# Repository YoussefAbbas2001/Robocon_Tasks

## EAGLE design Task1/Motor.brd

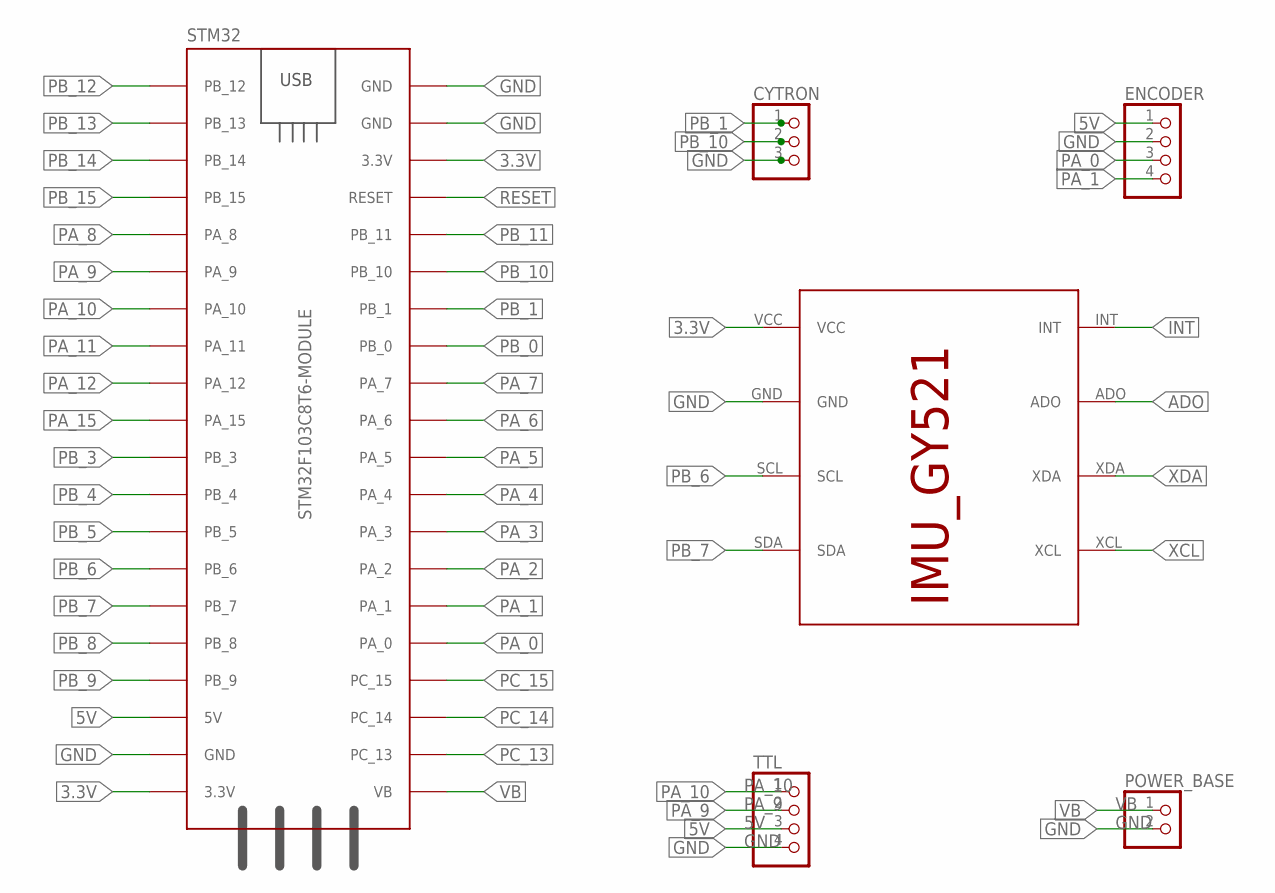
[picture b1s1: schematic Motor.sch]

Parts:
CYTRON: PINHD-3_DATA; 1X03_DATA
ENCODER: PINHD-4_DATA; 1X04_DATA
IMU: IMU_ROBOCON_GY521; IMU_GY521
POWER_BASE: PINHD-2_DATA; 1X02_DATA
STM32: STM32F103C8T6-MODULE
TTL: PINHD-4_DATA; 1X04_DATA

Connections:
3.3V: IMU.VCC, STM32.3.3V_1 (3.3V), STM32.3.3V_2 (3.3V)
5V: ENCODER.1, STM32.5V, TTL.3
ADO: IMU.ADO
GND: CYTRON.3, ENCODER.2, IMU.GND, POWER_BASE.2, STM32.GND_1 (GND), STM32.GND_2 (GND), STM32.GND_3 (GND), TTL.4
INT: IMU.INT
PA_0: ENCODER.3, STM32.PA_0
PA_1: ENCODER.4, STM32.PA_1
PA_2: STM32.PA_2
PA_3: STM32.PA_3
PA_4: STM32.PA_4
PA_5: STM32.PA_5
PA_6: STM32.PA_6
PA_7: STM32.PA_7
PA_8: STM32.PA_8
PA_9: STM32.PA_9, TTL.2
PA_10: STM32.PA_10, TTL.1
PA_11: STM32.PA_11
PA_12: STM32.PA_12
PA_15: STM32.PA_15
PB_0: STM32.PB_0
PB_1: CYTRON.1, STM32.PB_1
PB_3: STM32.PB_3
PB_4: STM32.PB_4
PB_5: STM32.PB_5
PB_6: IMU.SCL, STM32.PB_6
PB_7: IMU.SDA, STM32.PB_7
PB_8: STM32.PB_8
PB_9: STM32.PB_9
PB_10: CYTRON.2, STM32.PB_10
PB_11: STM32.PB_11
PB_12: STM32.PB_12
PB_13: STM32.PB_13
PB_14: STM32.PB_14
PB_15: STM32.PB_15
PC_13: STM32.PC_13
PC_14: STM32.PC_14
PC_15: STM32.PC_15
RESET: STM32.RESET
VB: POWER_BASE.1, STM32.VB
XCL: IMU.XCL
XDA: IMU.XDA

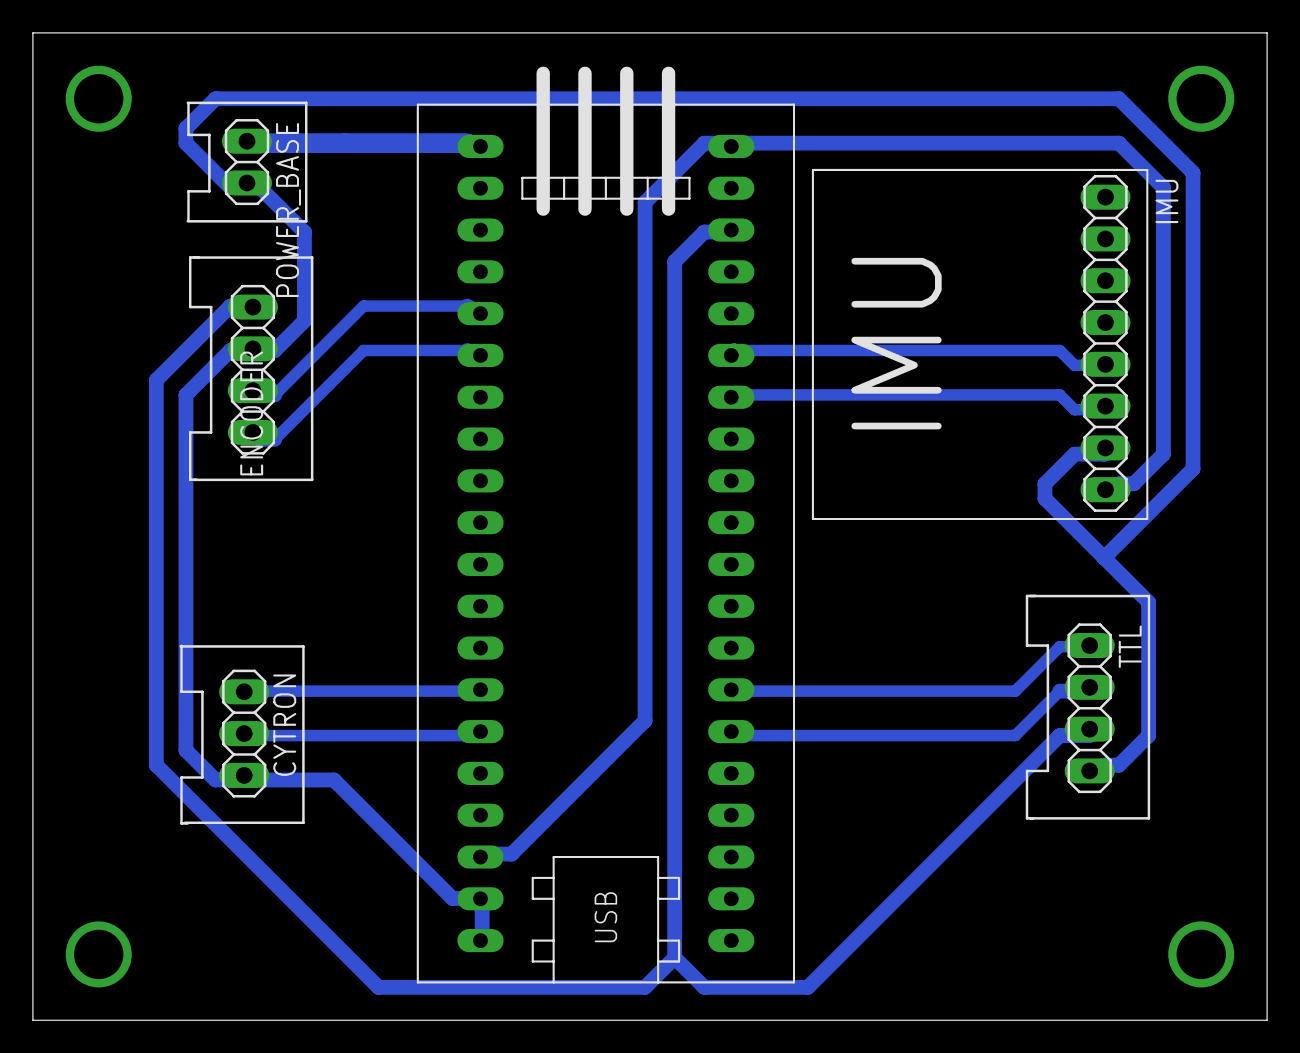
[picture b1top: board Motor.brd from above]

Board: 2 copper layers, 75.0 x 60.0 mm, 6 parts (0 on the bottom side), 12 nets.

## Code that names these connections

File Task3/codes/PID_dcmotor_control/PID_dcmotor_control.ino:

/*
Author : Youssef Abbas 
Date   : 6/11/2021
About  : PID control DC Motor
TO     : ROBOCON Traning Task3
*/
//#include <ros.h>
//#include <std_msgs/Float64.h>

#define SIGNAL_A PA_0  //PA_0
#define SIGNAL_B PA_1  //PA_1
#define PWM      PB_10 //PB_10
#define DIR      PB_1  //PB_1
#define PWM_LIM  65536 //Limit of PWM signal
#define PPRC     512   //Pulse Per Revolution Cycle
#define MIN      60    //minute

//ros::NodeHandle nh;
//float target;
//void callback( const std_msgs::Float64& msg){ target = msg.data;}
//ros::Subscriber<std_msgs::Float64> sub("drive_motor", &callback );

double  pwm      ;         //PWM signal  of MOTOR
double  control  ;         //Control Signal Out of PID control 
double  set_point= 0    ;  //target speed
double  integral = 0    ;  //Summation of error Added to control signal to overcome Steady-State Error
double  diff     = 0    ;  //Derivative term
double  kp =  2  ;         //Proportional Constant
double  ki =  1  ;         //Intergral Constant
double  kd =  1  ;         //Derivative Constant
double  error=0  ;         //Error Signal (E = T - P)
double  prev_e=0 ;         //previous error (to compute Derivaitve term)
double  velocity ;         //Current Velocity of Motor
double  distance ;         //Distance cutted by Motor in Meter
double  delta_t  ;         //Change time = (current time) - (previous time)
double  delta_e  ;         //Change Error= (Current error)- (previous error)
double  prev_t=0 ;         //Previous time used to computer delta of time 
double  curr_t=0 ;         //Current time usef to compute  delta of time
double  counter=0;         //Counter of Encoder
double  prev_c=0 ;         //Previous Count used to compute delta of distance
double  curr_c=0 ;         //Current Count used to compute delta of distance
double  delta_c=0;         //Change in Distance = (Current Count) - (Previous Count)

HardwareSerial Serial3(PB11, PB10);

void setup() 
{
  Serial3.begin(9600);
//  nh.initNode();                   //intialize node to subscribe
//  nh.subscribe(sub);               //subscribe data
  pinMode(SIGNAL_A, INPUT_PULLUP);   //Encoder A
  pinMode(SIGNAL_B, INPUT_PULLUP);   //Encoder B
  pinMode(DIR,OUTPUT);               //Dirction of DC MOTOR
  pinMode(PWM,OUTPUT);               //Speed of DC MOTOR


  set_point = 0  ;            //get set point from published data  
  attachInterrupt(digitalPinToInterrupt(SIGNAL_A), ISR_A, CHANGE);
  attachInterrupt(digitalPinToInterrupt(SIGNAL_B), ISR_B, CHANGE);

//  (nh.getHardware()->setPort(&Serial1));
//  (nh.getHardware()->setBaud(115200));
//  nh.initNode();
//  nh.subscribe(target);
}

void loop()
{
  calc();                                          //get (Velocity) and (delta time) 

  if (control<0)                                   //When Control is negative (Exceed Target) 
  {
      digitalWrite(DIR , HIGH)
  }
  else if (control>0) 
  {
      digitalWrite(DIR,LOW)
  }   
  pwm = abs(control);                              //Absolute value of Control
  if(pwm > PWM_LIM)                                //if Control signal exceed max PWM
     pwm = PWM_LIM;                                //Maximum PWM signal in Arduino UNO
  analogWrite(PWM,pwm);                            // Motor speed

  Serial3.print("rpm: ");
  Serial3.println(error);
  Serial3.print("error :");
  Serial3.println(pwm );
  Serial3.print("Speed : ");
  Serial3.print(velocity);
  Serial3.println(",");
  delay(50);

}





void ISR_A()
{
  if (digitalRead(SIGNAL_A) != digitalRead(SIGNAL_B))
    counter++  ;
  else
    counter--  ;
}

void ISR_B()
{
  if (digitalRead(SIGNAL_A) == digitalRead(SIGNAL_B))
    counter++   ;
  else
    counter--  ;
}


void get_speed()
{
  curr_t     = millis();
  curr_c     = counter;
  delta_t    =(curr_t - prev_t)         ;          //Change in time  (ms)
  delta_c    =(curr_c - prev_c)         ;          //Change in count (pulse)
  velocity   =(delta_c)/(delta_t) *1000 ;          //curr_speed      (pulse/s)  
  velocity   =(velocity/PPRC)*MIN       ;          //curr_speed      (RPM)
  
  error     = set_point - velocity;                //error = <Target Velocity> - <Current Velocity>    
  delta_e   = error-prev_e;                        //Change in Error
  integral  = integral + ki*error*delta_t;         //Interation of Error to overcome Steady-state error
  diff      = delta_e/delta_t ;                    //Derivative Term to overcome Damping
  control   = kp*error + integral + kd*diff;       //Control Equation
//  control   = 100*control;                       //Map Control Signal to get better Response

//Privous Values
  prev_e     = error;                           
  prev_c     = curr_c;         
  prev_t     = curr_t;

}

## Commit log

2021-10-25 :first task
2021-10-25 :first_task2
2021-10-25 :first_task3
2021-10-26 :first_task4
2021-11-01 Task2_first
2021-11-04 IMU_LIB
2021-11-06 'Task3'
2021-11-06 Remove Task23
2021-11-06 'Task3_IMU_with_lib'
2021-11-07 add ros once
2021-11-15 Yaw_added
